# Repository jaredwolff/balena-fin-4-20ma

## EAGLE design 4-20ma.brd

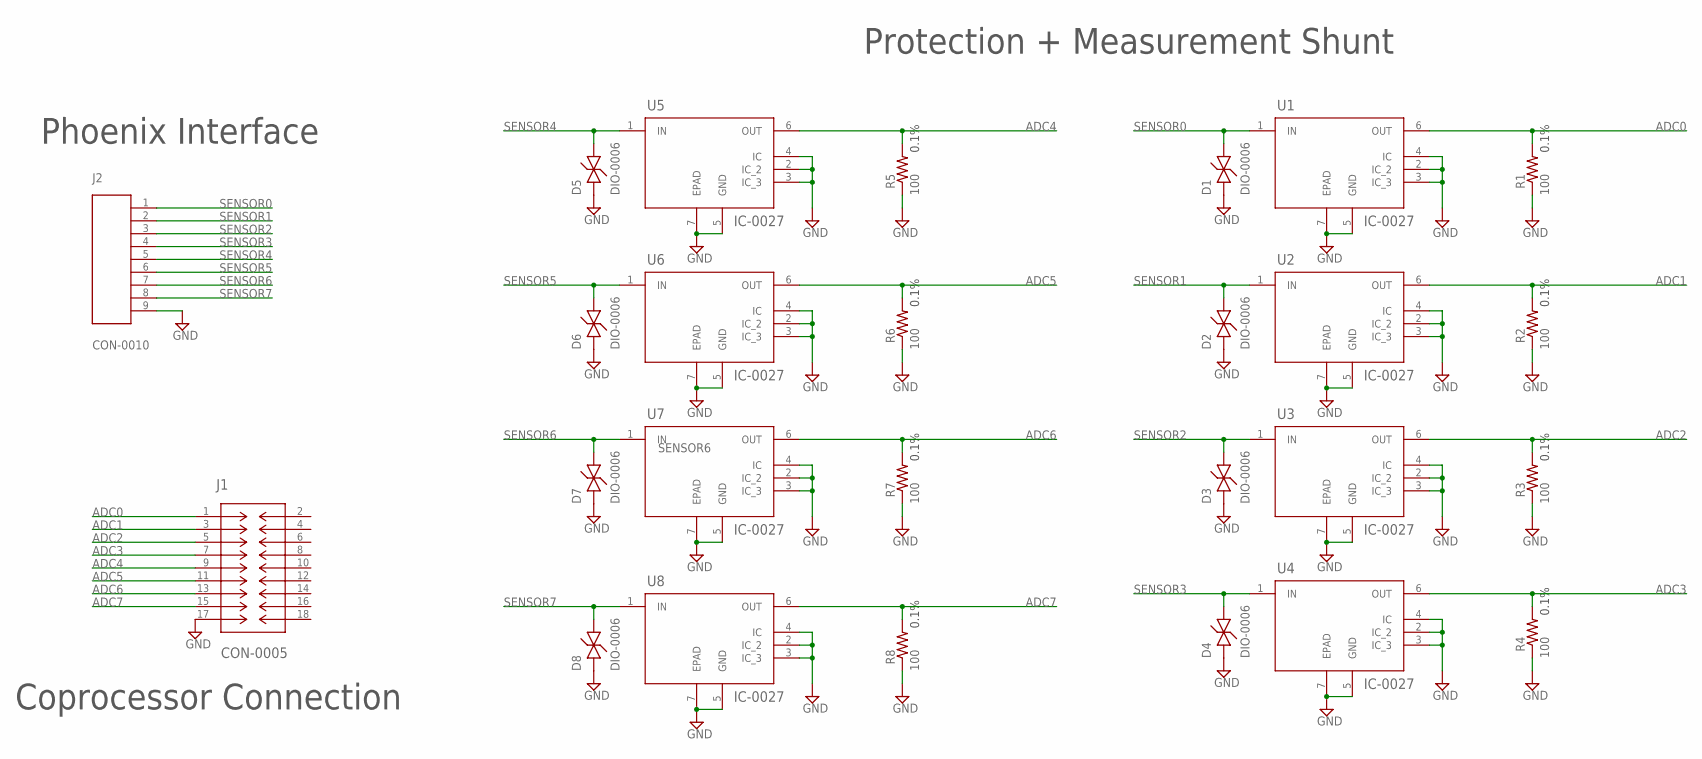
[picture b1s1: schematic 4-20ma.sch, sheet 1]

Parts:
D1, D2, D3, D4, D5, D6, D7, D8: DIO-0006; SMASERIES
J1: CON-0005; CON18_2X9_TU_SSQ
J2: CON-0010; CON-B9B-ZR
R1, R2, R3, R4, R5, R6, R7, R8: 100; R0603
U1, U2, U3, U4, U5, U6, U7, U8: IC-0027; 21-0137I_T633-2

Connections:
ADC0: J1.1, R1.2, U1.6 (OUT)
ADC1: J1.3, R2.2, U2.6 (OUT)
ADC2: J1.5, R3.2, U3.6 (OUT)
ADC3: J1.7, R4.2, U4.6 (OUT)
ADC4: J1.9, R5.2, U5.6 (OUT)
ADC5: J1.11, R6.2, U6.6 (OUT)
ADC6: J1.13, R7.2, U7.6 (OUT)
ADC7: J1.15, R8.2, U8.6 (OUT)
GND: D1.1, D2.1, D3.1, D4.1, D5.1, D6.1, D7.1, D8.1, J1.17, J2.9, R1.1, R2.1, R3.1, R4.1, R5.1, R6.1, R7.1, R8.1, U1.2 (IC_2), U1.3 (IC_3), U1.4 (IC), U1.5 (GND), U1.7 (EPAD), U2.2 (IC_2), U2.3 (IC_3), U2.4 (IC), U2.5 (GND), U2.7 (EPAD), U3.2 (IC_2), U3.3 (IC_3), U3.4 (IC), U3.5 (GND), U3.7 (EPAD), U4.2 (IC_2), U4.3 (IC_3), U4.4 (IC), U4.5 (GND), U4.7 (EPAD), U5.2 (IC_2), U5.3 (IC_3), U5.4 (IC), U5.5 (GND), U5.7 (EPAD), U6.2 (IC_2), U6.3 (IC_3), U6.4 (IC), U6.5 (GND), U6.7 (EPAD), U7.2 (IC_2), U7.3 (IC_3), U7.4 (IC), U7.5 (GND), U7.7 (EPAD), U8.2 (IC_2), U8.3 (IC_3), U8.4 (IC), U8.5 (GND), U8.7 (EPAD); also elsewhere on the board
SENSOR0: D1.2, J2.1, U1.1 (IN)
SENSOR1: D2.2, J2.2, U2.1 (IN)
SENSOR2: D3.2, J2.3, U3.1 (IN)
SENSOR3: D4.2, J2.4, U4.1 (IN)
SENSOR4: D5.2, J2.5, U5.1 (IN)
SENSOR5: D6.2, J2.6, U6.1 (IN)
SENSOR6: D7.2, J2.7, U7.1 (IN)
SENSOR7: D8.2, J2.8, U8.1 (IN)

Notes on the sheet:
Protection + Measurement Shunt
Coprocessor Connection
Phoenix Interface

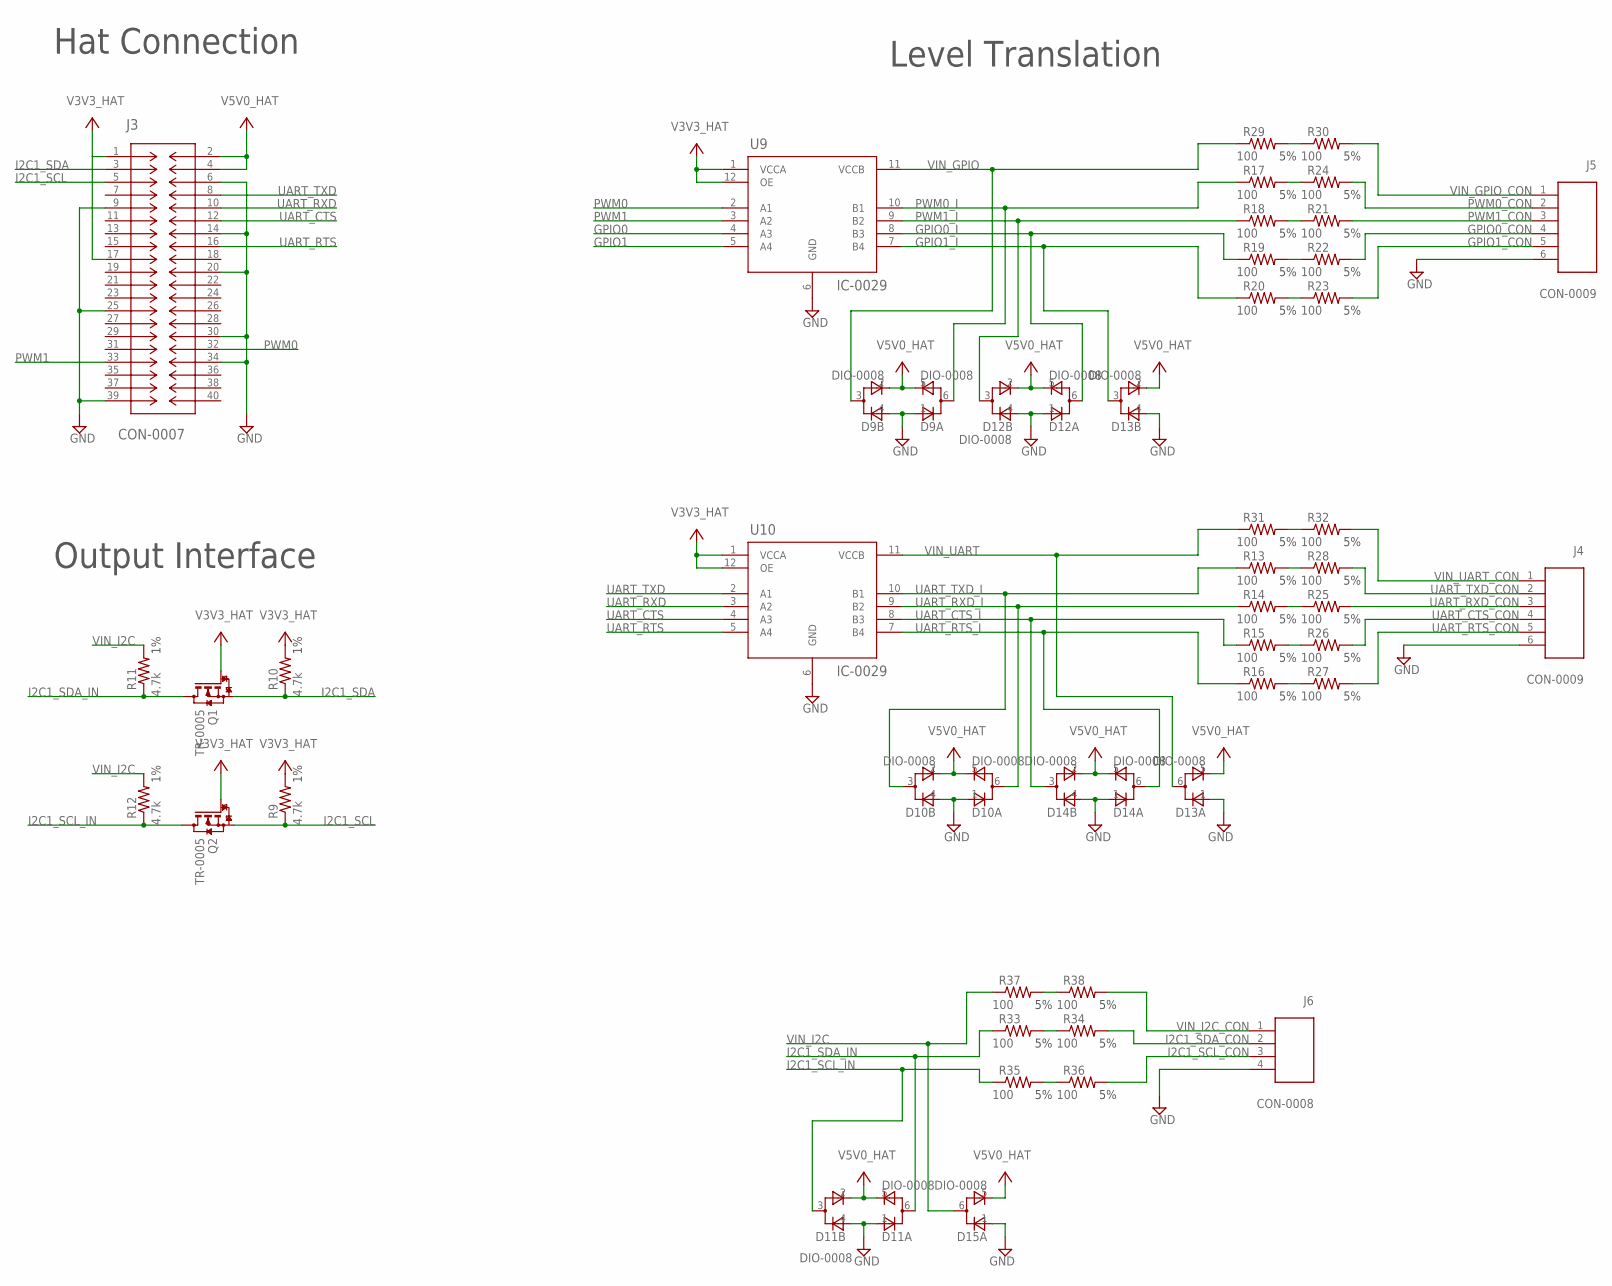
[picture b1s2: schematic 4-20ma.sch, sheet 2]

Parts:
D9, D10, D11, D12, D13, D14, D15: DIO-0008; SOT-563
J3: CON-0007; CON40_2X20_TU_SSQ
J4, J5: CON-0009; CON-S6B-ZR
J6: CON-0008; CON-S4B-ZR
Q1, Q2: TR-0005; SOT323
R9, R10, R11, R12: 4.7k; R0603
R13, R14, R15, R16, R17, R18, R19, R20, R21, R22, R23, R24, R25, R26, R27, R28, R29, R30, R31, R32, R33, R34, R35, R36, R37, R38: 100; R0603
U9, U10: IC-0029; RUT12

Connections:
GND: D9.1 (A), D9.4 (A), D10.1 (A), D10.4 (A), D11.1 (A), D11.4 (A), D12.1 (A), D12.4 (A), D13.1 (A), D13.4 (A), D14.1 (A), D14.4 (A), D15.1 (A), J3.6, J3.9, J3.14, J3.20, J3.25, J3.30, J3.34, J3.39, J4.6, J5.6, J6.4, U9.6 (GND), U10.6 (GND); also elsewhere on the board
GPIO0: U9.4 (A3)
GPIO0_CON: J5.4, R22.2
GPIO0_I: D12.6 (AC), R19.1, U9.8 (B3)
GPIO0_II: R19.2, R22.1
GPIO1: U9.5 (A4)
GPIO1_CON: J5.5, R23.2
GPIO1_I: D13.3 (AC), R20.1, U9.7 (B4)
GPIO1_II: R20.2, R23.1
I2C1_SCL: J3.5, Q2.S, R9.1
I2C1_SCL_CON: J6.3, R36.2
I2C1_SCL_IN: D11.3 (AC), Q2.D, R12.1, R35.1
I2C1_SDA: J3.3, Q1.S, R10.1
I2C1_SDA_CON: J6.2, R34.2
I2C1_SDA_IN: D11.6 (AC), Q1.D, R11.1, R33.1
unnamed: R13.2, R28.1
unnamed: R14.2, R25.1
unnamed: R15.2, R26.1
unnamed: R16.2, R27.1
PWM0: J3.32, U9.2 (A1)
PWM0_CON: J5.2, R24.2
PWM0_I: D9.6 (AC), R17.1, U9.10 (B1)
PWM0_II: R17.2, R24.1
PWM0_II1: R29.2, R30.1
PWM0_II2: R31.2, R32.1
PWM0_II3: R33.2, R34.1
PWM0_II4: R35.2, R36.1
PWM0_II5: R37.2, R38.1
PWM1: J3.33, U9.3 (A2)
PWM1_CON: J5.3, R21.2
PWM1_I: D12.3 (AC), R18.1, U9.9 (B2)
PWM1_II: R18.2, R21.1
UART_CTS: J3.12, U10.4 (A3)
UART_CTS_CON: J4.4, R26.2
UART_CTS_I: D14.3 (AC), R15.1, U10.8 (B3)
UART_RTS: J3.16, U10.5 (A4)
UART_RTS_CON: J4.5, R27.2
UART_RTS_I: D14.6 (AC), R16.1, U10.7 (B4)
UART_RXD: J3.10, U10.3 (A2)
UART_RXD_CON: J4.3, R25.2
UART_RXD_I: D10.6 (AC), R14.1, U10.9 (B2)
UART_TXD: J3.8, U10.2 (A1)
UART_TXD_CON: J4.2, R28.2
UART_TXD_I: D10.3 (AC), R13.1, U10.10 (B1)
V3V3_HAT: J3.1, J3.17, Q1.G, Q2.G, R9.2, R10.2, U9.1 (VCCA), U9.12 (OE), U10.1 (VCCA), U10.12 (OE)
V5V0_HAT: D9.2 (C), D9.5 (C), D10.2 (C), D10.5 (C), D11.2 (C), D11.5 (C), D12.2 (C), D12.5 (C), D13.2 (C), D13.5 (C), D14.2 (C), D14.5 (C), D15.5 (C), J3.2, J3.4
VIN_GPIO: D9.3 (AC), R29.1, U9.11 (VCCB)
VIN_GPIO_CON: J5.1, R30.2
VIN_I2C: D15.6 (AC), R11.2, R12.2, R37.1
VIN_I2C_CON: J6.1, R38.2
VIN_UART: D13.6 (AC), R31.1, U10.11 (VCCB)
VIN_UART_CON: J4.1, R32.2

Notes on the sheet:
Output Interface
Hat Connection
Level Translation

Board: 2 copper layers, 71 parts (0 on the bottom side), 66 nets, no tracks yet.

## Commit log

2018-10-30 First commit.
2018-10-30 Create LICENSE
